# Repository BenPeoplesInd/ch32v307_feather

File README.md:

# ch32v307_feather
Feather-ish board for ch32v307rct6

This is a rough pass at a ch32v307 feather using the 64-pin variant of the CH32V307.   

At this moment it's untested (I'm ordering them now).    USB-C for the programming adapter.

A few notes vs. the official feather:

- I've omitted the LiPo stack
- Current vreg is only 100mA
- BOOT button connects BOOT0 to 3.3V to enable bootloader over USB
- There's no debug via USB (unless you write one)
- No SWD breakout
- Includes 5.1k resistors for USB-C PD
- All the GPIOs are ADC capable
- Did not breakout the ethernet pins anywhere, which might actually be super useful.  
- No status/indicator LEDs
- SPI is SPI2
- i2c is also USB2
- Schematic is messy and poorly documented

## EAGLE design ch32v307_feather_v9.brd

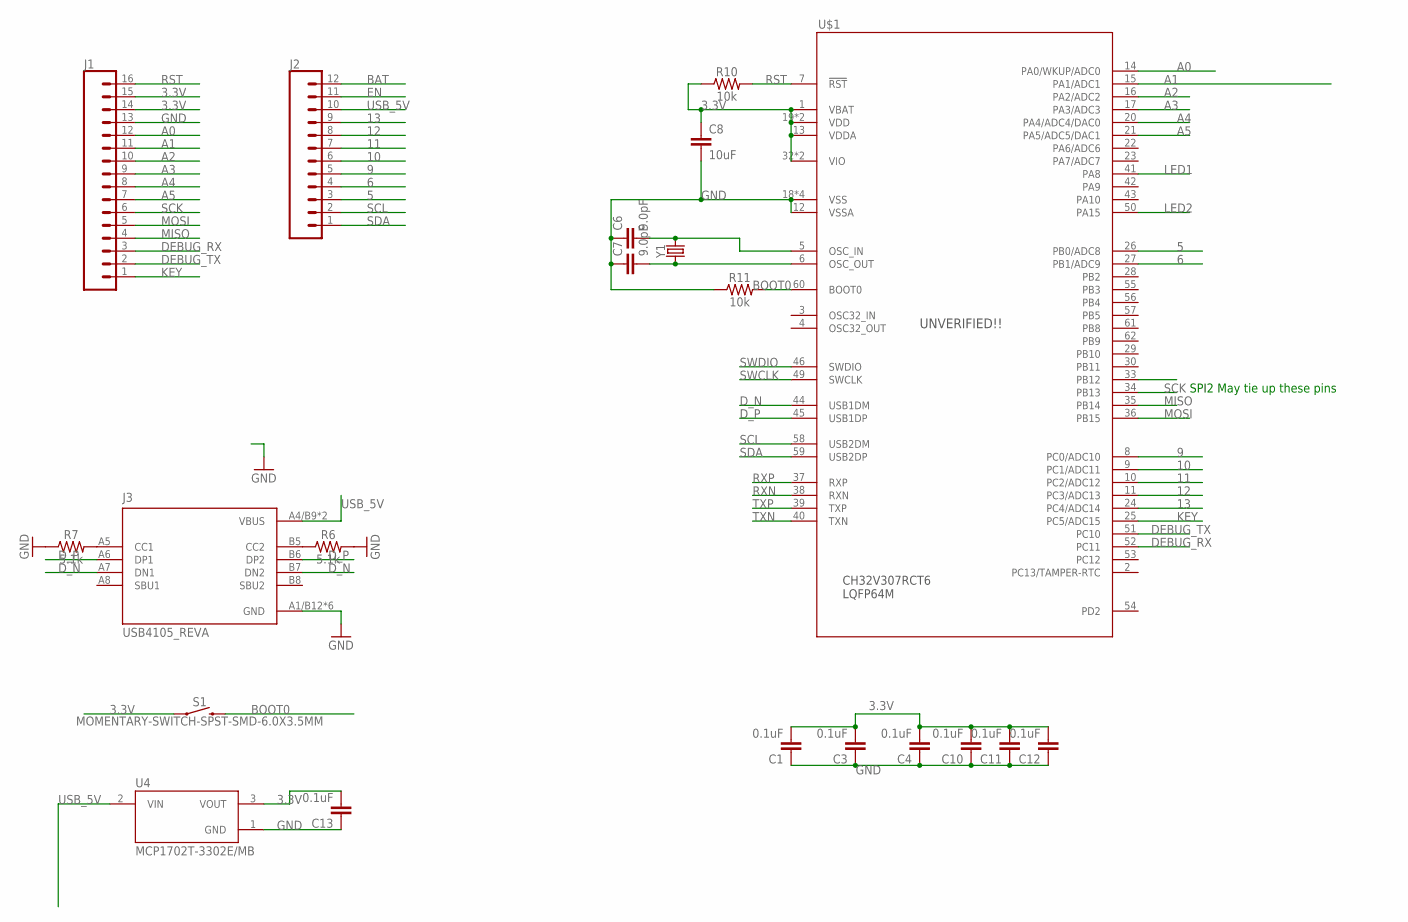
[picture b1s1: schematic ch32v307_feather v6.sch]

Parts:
C1, C3, C4, C10, C11, C12, C13: 0.1uF; 0603-CAP
C6, C7: 9.0pF; 0603
C8: 10uF; 1210
J1: CONN_16; 1X16
J2: CONN_12; 1X12
J3: USB4105_REVA; GCT_USB4105_REVA
R6, R7: 5.1k; 0603
R10, R11: 10k; 0603
S1: MOMENTARY-SWITCH-SPST-SMD-6.0X3.5MM; TACTILE_SWITCH_SMD_6.0X3.5MM
U4: MCP1702T-3302E/MB; REG_MCP1702T-3302E/MB
U$1: CH32V307RCT6; LQFP64M
Y1: CRYSTALSMD-3.2X2.5; CRYSTAL-SMD-3.2X2.5MM

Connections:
3.3V: C1.2, C3.2, C4.2, C8.1, C10.2, C11.2, C12.2, C13.2, J1.14, J1.15, R10.1, S1.1, U4.3 (VOUT), U$1.1 (VBAT), U$1.13 (VDDA), U$1.19 (VDD), U$1.32 (VIO), U$1.48 (VDD), U$1.64 (VIO)
5: J2.3, U$1.26 (PB0/ADC8)
6: J2.4, U$1.27 (PB1/ADC9)
9: J2.5, U$1.8 (PC0/ADC10)
10: J2.6, U$1.9 (PC1/ADC11)
11: J2.7, U$1.10 (PC2/ADC12)
12: J2.8, U$1.11 (PC3/ADC13)
13: J2.9, U$1.24 (PC4/ADC14)
A0: J1.12, U$1.14 (PA0/WKUP/ADC0)
A1: J1.11, U$1.15 (PA1/ADC1)
A2: J1.10, U$1.16 (PA2/ADC2)
A3: J1.9, U$1.17 (PA3/ADC3)
A4: J1.8, U$1.20 (PA4/ADC4/DAC0)
A5: J1.7, U$1.21 (PA5/ADC5/DAC1)
BAT: J2.12
BOOT0: R11.2, S1.2, U$1.60 (BOOT0)
DEBUG_RX: J1.3, U$1.52 (PC11)
DEBUG_TX: J1.2, U$1.51 (PC10)
D_N: J3.A7 (DN1), J3.B7 (DN2), U$1.44 (USB1DM)
D_P: J3.A6 (DP1), J3.B6 (DP2), U$1.45 (USB1DP)
EN: J2.11
GND: C1.1, C3.1, C4.1, C6.1, C7.1, C8.2, C10.1, C11.1, C12.1, C13.1, J1.13, J3.A1/B12 (GND), J3.B1/A12 (GND), J3.G1 (GND), J3.G2 (GND), J3.G3 (GND), J3.G4 (GND), R6.2, R7.1, R11.1, U4.1 (GND), U$1.12 (VSSA), U$1.18 (VSS), U$1.31 (VSS), U$1.47 (VSS), U$1.63 (VSS)
KEY: J1.1, U$1.25 (PC5/ADC15)
LED1: U$1.41 (PA8)
LED2: U$1.50 (PA15)
MISO: J1.4, U$1.35 (PB14)
MOSI: J1.5, U$1.36 (PB15)
unnamed: C6.2, U$1.5 (OSC_IN), Y1.3 (2)
unnamed: C7.2, U$1.6 (OSC_OUT), Y1.1
unnamed: J3.B5 (CC2), R6.1
unnamed: J3.A5 (CC1), R7.2
RST: J1.16, R10.2, U$1.7 (!RST)
RXN: U$1.38 (RXN)
RXP: U$1.37 (RXP)
SCK: J1.6, U$1.34 (PB13)
SCL: J2.2, U$1.58 (USB2DM)
SDA: J2.1, U$1.59 (USB2DP)
SWCLK: U$1.49 (SWCLK)
SWDIO: U$1.46 (SWDIO)
TXN: U$1.40 (TXN)
TXP: U$1.39 (TXP)
USB_5V: J2.10, J3.A4/B9 (VBUS), J3.B4/A9 (VBUS), U4.2 (VIN)

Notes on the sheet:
SPI2 May tie up these pins

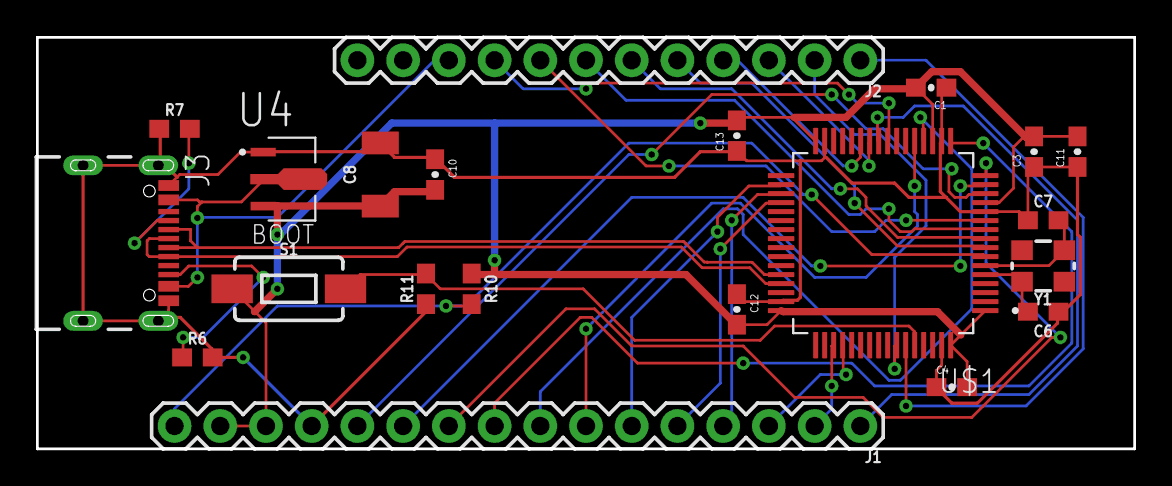
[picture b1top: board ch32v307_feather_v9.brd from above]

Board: 2 copper layers, 61.0 x 22.9 mm, 21 parts (0 on the bottom side), 32 nets.

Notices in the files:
parts and their libraries:
SparkFun-Connectors: Licensing: Creative Commons ShareAlike 4.0 International - https://creativecommons.org/licenses/by-sa/4.0
SparkFun-Aesthetics: Licensing: CC v3.0 Share-Alike You are welcome to use this library for commercial purposes.
